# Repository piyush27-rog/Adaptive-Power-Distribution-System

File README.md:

# Adaptive Power Distribution System

A 12 V DC power distribution system designed to provide regulated **5 V and 3.3 V outputs** for multiple loads, with input protection and individual output protection.

## Key Specifications

| Parameter | Specification |
|---|---|
| Input | 12 V DC |
| 5 V Output | 5 V / 1.5 A total |
| 3.3 V Output | 3.3 V / 0.3 A |
| Regulators | LM2596S-5 / LM2596S-3.3 |
| Input Protection | 3 A Fuse + Reverse Polarity Protection |
| Output Protection | Individual Polyfuses |
| Simulation | NI Multisim |
| PCB Design | KiCad |

## Highlights

- Dual regulated power rails: **5 V and 3.3 V**
- Reverse-polarity and overcurrent protection
- Individual protected output branches
- Custom schematic and PCB layout
- Simulation and waveform verification
- Engineering calculations and BOM included

## Project Files

- **Multisim** — Circuit simulation
- **KiCad** — Schematic and PCB files
- **Documentation** — BOM, engineering calculations and design explanation
- **Images** — Schematic and PCB views
- **Simulation** — Simulation results

## Tools

**NI Multisim · KiCad**

## Author

**Piyush Thote**

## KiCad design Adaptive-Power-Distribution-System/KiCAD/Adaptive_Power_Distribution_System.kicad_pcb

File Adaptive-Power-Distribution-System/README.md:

# Adaptive Power Distribution System

A 12 V DC power distribution system designed to provide regulated **5 V and 3.3 V outputs** for multiple loads, with input protection and individual output protection.

## Key Specifications

| Parameter | Specification |
|---|---|
| Input | 12 V DC |
| 5 V Output | 5 V / 1.5 A total |
| 3.3 V Output | 3.3 V / 0.3 A |
| Regulators | LM2596S-5 / LM2596S-3.3 |
| Input Protection | 3 A Fuse + Reverse Polarity Protection |
| Output Protection | Individual Polyfuses |
| Simulation | NI Multisim |
| PCB Design | KiCad |

## Highlights

- Dual regulated power rails: **5 V and 3.3 V**
- Reverse-polarity and overcurrent protection
- Individual protected output branches
- Custom schematic and PCB layout
- Simulation and waveform verification
- Engineering calculations and BOM included

## Project Files

- **Multisim** — Circuit simulation
- **KiCad** — Schematic and PCB files
- **Documentation** — BOM, engineering calculations and design explanation
- **Images** — Schematic and PCB views
- **Simulation** — Simulation results

## Tools

**NI Multisim · KiCad**

## Author

**Piyush Thote**

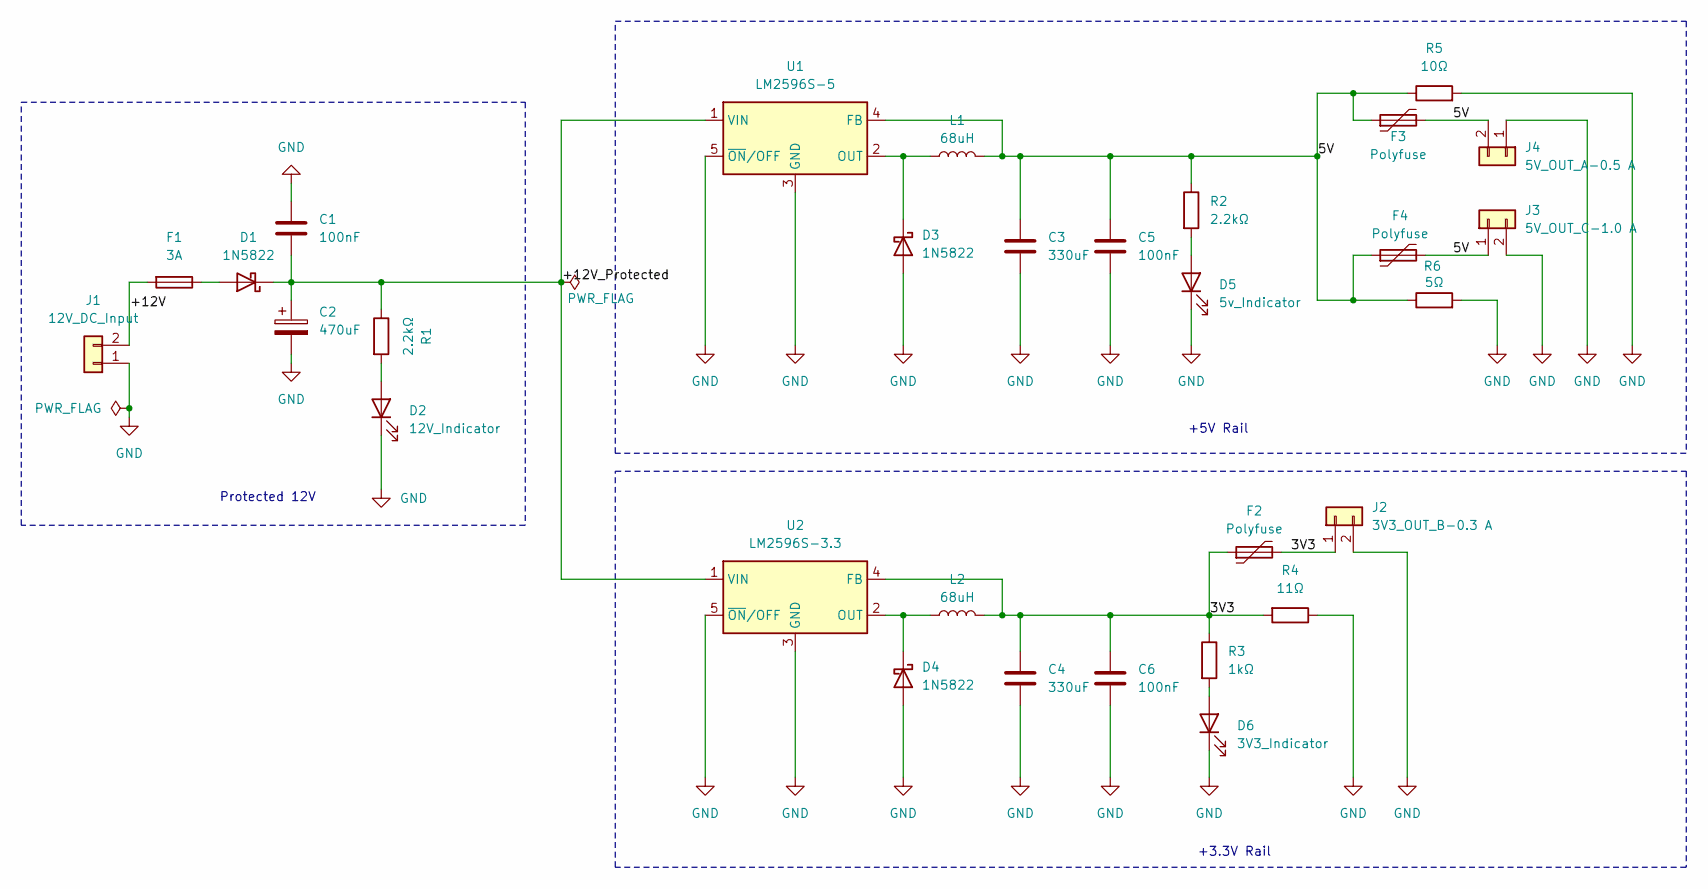
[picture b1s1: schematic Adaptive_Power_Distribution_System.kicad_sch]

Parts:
C1, C5, C6: 100nF; C_Disc_D5.0mm_W2.5mm_P5.00mm
C2: 470uF; CP_Radial_D8.0mm_P3.50mm
C3, C4: 330uF; C_Radial_D8.0mm_H11.5mm_P3.50mm
D1, D3, D4: 1N5822; D_DO-201AD_P15.24mm_Horizontal
D2: 12V_Indicator; LED_D5.0mm
D5: 5v_Indicator; LED_D5.0mm
D6: 3V3_Indicator; LED_D5.0mm
F1: 3A; Fuseholder_Clip-5x20mm_Bel_FC-203-22_Lateral_P17.80x5.00mm_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
F2: Polyfuse; Fuse_Bourns_MF-RHT400
F3: Polyfuse; Fuse_Bourns_MF-RHT070
F4: Polyfuse; Fuse_Bourns_MF-RHT1300
J1: 12V_DC_Input; Altech_AK100_1x02_P5.00mm
J2: 3V3_OUT_B-0.3 A; Altech_AK100_1x02_P5.00mm
J3: 5V_OUT_C-1.0 A; Altech_AK100_1x02_P5.00mm
J4: 5V_OUT_A-0.5 A; Altech_AK100_1x02_P5.00mm
L1: 68uH; L_Radial_D16.8mm_P12.70mm_Vishay_IHB-1
L2: 68uH; L_Radial_D21.0mm_P14.61mm_Vishay_IHB-2
R1, R2: 2.2kΩ; R_Axial_DIN0207_L6.3mm_D2.5mm_P10.16mm_Horizontal
R3: 1kΩ; R_Axial_DIN0207_L6.3mm_D2.5mm_P10.16mm_Horizontal
R4: 11Ω; R_Axial_Power_L20.0mm_W6.4mm_P22.40mm
R5: 10Ω; R_Axial_Power_L25.0mm_W6.4mm_P27.94mm
R6: 5Ω; R_Axial_Power_L38.0mm_W9.0mm_P40.64mm
U1: LM2596S-5; TO-263-5_TabPin3
U2: LM2596S-3.3; TO-263-5_TabPin3

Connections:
/3V3: C4.1, C6.1, F2.1, F2.2, J2.1, L2.2, R3.1, R4.2, U2.4 (FB)
/5V: C3.1, C5.1, F3.1, F3.2, F4.1, F4.2, J3.1, J4.2, L1.2, R2.1, R5.1, R6.1, U1.4 (FB)
/+12V: F1.2, J1.2
/+12V_Protected: C1.2, C2.1, D1.1 (K), R1.1, U1.1 (VIN), U2.1 (VIN)
GND: C1.1, C2.2, C3.2, C4.2, C5.2, C6.2, D2.1 (K), D3.2 (A), D4.2 (A), D5.1 (K), D6.1 (K), J1.1, J2.2, J3.2, J4.1, R4.1, R5.2, R6.2, U1.3 (GND), U1.5 (~ON/OFF), U2.3 (GND), U2.5 (~ON/OFF)
unnamed: D1.2 (A), F1.1
unnamed: D2.2 (A), R1.2
unnamed: D3.1 (K), L1.1, U1.2 (OUT)
unnamed: D4.1 (K), L2.1, U2.2 (OUT)
unnamed: D5.2 (A), R2.2
unnamed: D6.2 (A), R3.2

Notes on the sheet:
+5V Rail
Protected 12V
+3.3V Rail

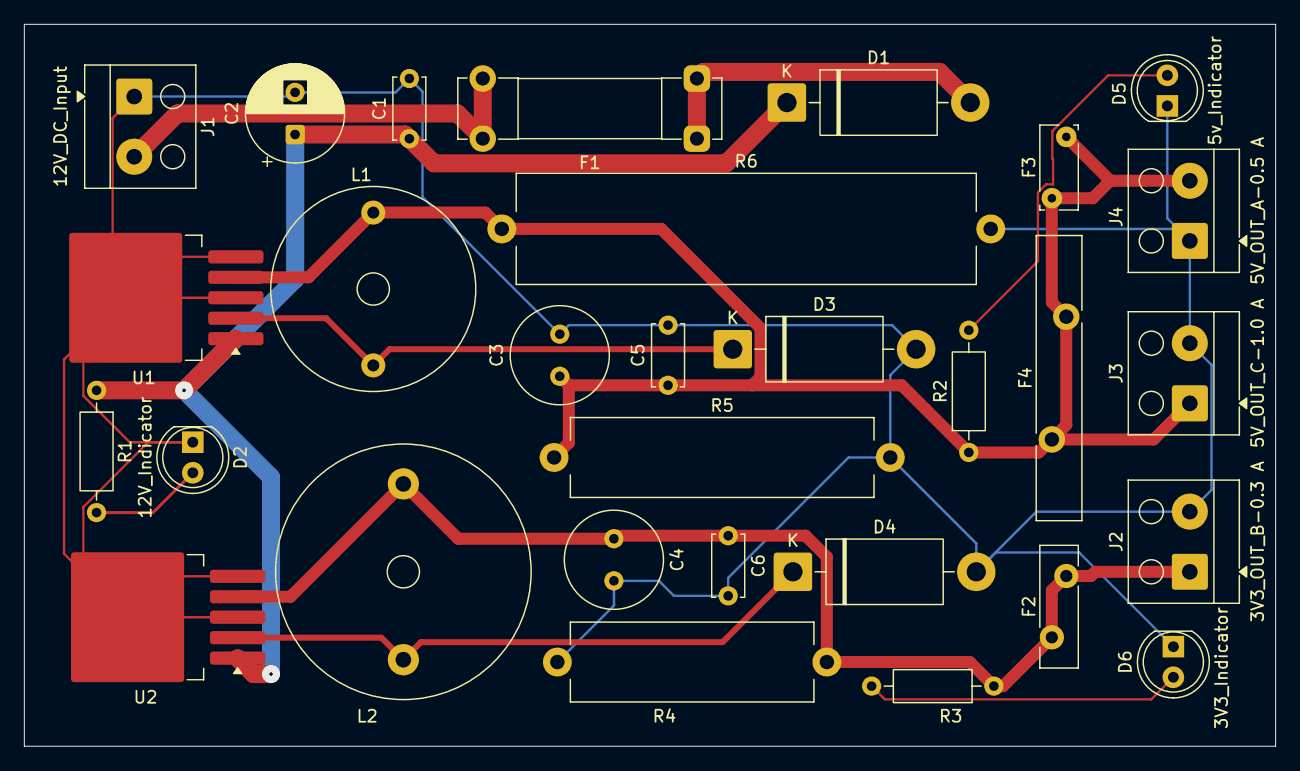
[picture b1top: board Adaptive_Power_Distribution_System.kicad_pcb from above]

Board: 2 copper layers, 104.0 x 60.0 mm, 30 parts (0 on the bottom side), 11 nets.
